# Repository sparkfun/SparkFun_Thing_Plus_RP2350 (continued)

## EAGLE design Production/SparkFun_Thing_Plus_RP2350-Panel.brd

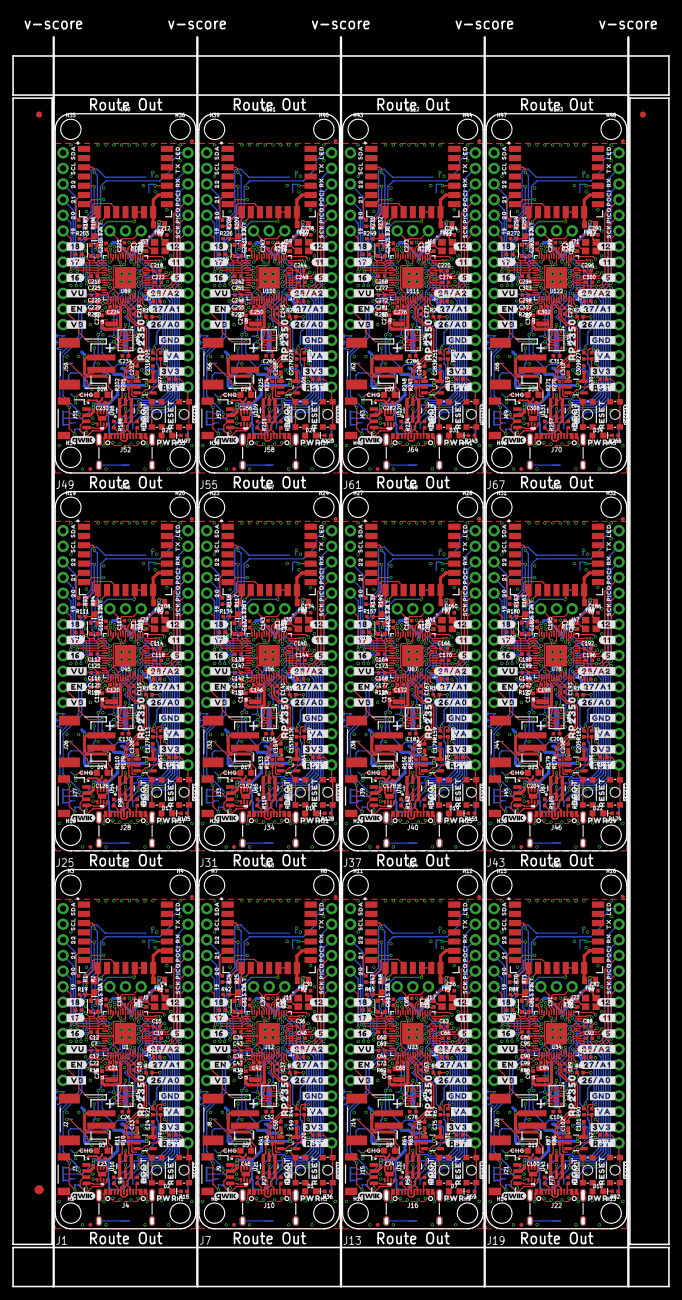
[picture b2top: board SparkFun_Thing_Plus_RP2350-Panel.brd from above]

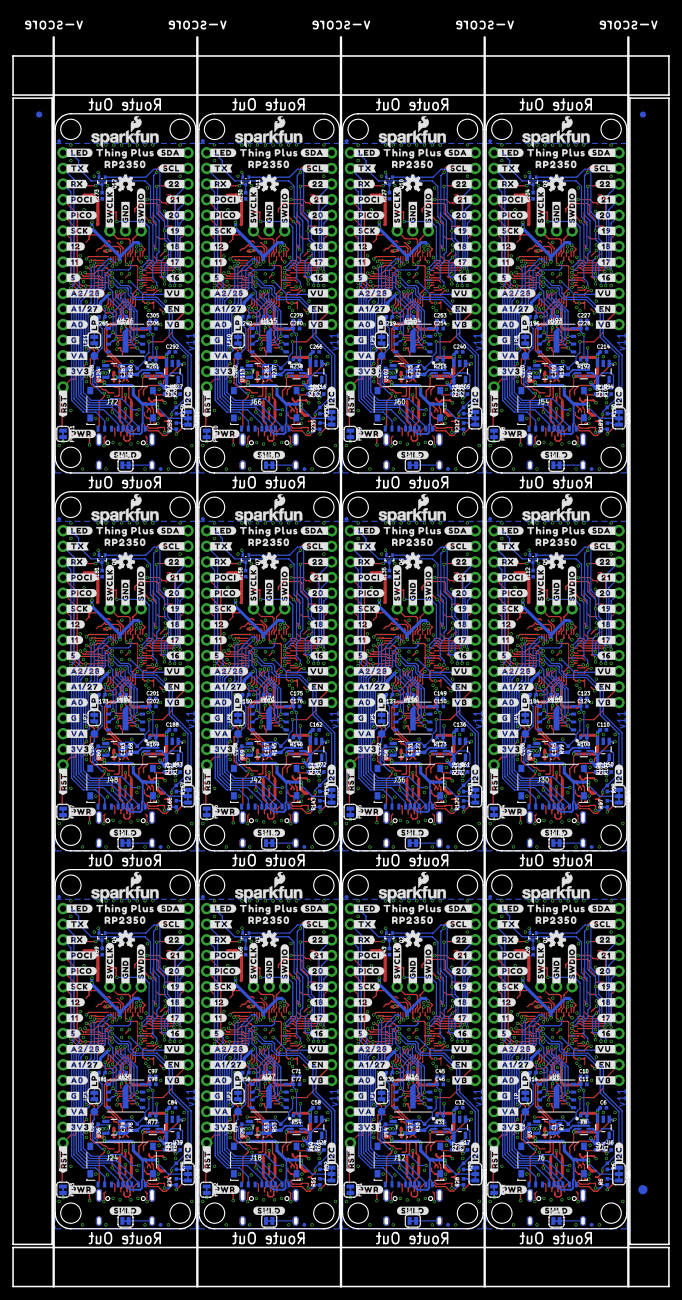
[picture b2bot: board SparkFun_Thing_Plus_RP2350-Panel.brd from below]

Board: 4 copper layers, 106.7 x 203.2 mm, 1950 parts (807 on the bottom side), 912 nets.

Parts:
BOOT, BOOT1, BOOT2, BOOT3, BOOT4, BOOT5, BOOT6, BOOT7, BOOT8, BOOT9, BOOT10, BOOT11: MOMENTARY-SWITCH-SPST-SMD-4.6X2.8MM; TACTILE_SWITCH_SMD_4.6X2.8MM
C1, C2, C5, C6, C10, C13, C22, C27, C28, C31, C32, C45, C47, C50, C53, C54, C57, C58, C71, C73, C76, C79, C80, C83, C84, C97, C99, C102, C105, C106, C109, C110, C123, C125, C128, C131, C132, C135, C136, C149, C151, C154, C157, C158, C161, C162, C175, C177, C180, C183, C184, C187, C188, C201, C203, C206, C209, C210, C213, C214, C227, C229, C232, C235, C236, C239, C240, C253, C255, C258, C261, C262, C265, C266, C279, C281, C284, C287, C288, C291, C292, C305, C307, C310: 2.2uF; 0402-TIGHT
C3, C4, C29, C30, C55, C56, C81, C82, C107, C108, C133, C134, C159, C160, C185, C186, C211, C212, C237, C238, C263, C264, C289, C290: 15pF; 0402-TIGHT
C7, C8, C9, C11, C12, C14, C15, C16, C17, C18, C19, C23, C25, C26, C33, C34, C35, C36, C37, C38, C39, C40, C43, C44, C46, C48, C51, C52, C59, C60, C61, C62, C63, C64, C65, C66, C69, C70, C72, C74, C77, C78, C85, C86, C87, C88, C89, C90, C91, C92, C95, C96, C98, C100, C103, C104, C111, C112, C113, C114, C115, C116, C117, C118, C121, C122, C124, C126, C129, C130, C137, C138, C139, C140, C141, C142, C143, C144, C147, C148, C150, C152, C155, C156, C163, C164, C165, C166, C167, C168, C169, C170, C173, C174, C176, C178, C181, C182, C189, C190, C191, C192, C193, C194, C195, C196, C199, C200, C202, C204, C207, C208, C215, C216, C217, C218, C219, C220, C221, C222, C225, C226, C228, C230, C233, C234, C241, C242, C243, C244, C245, C246, C247, C248, C251, C252, C254, C256, C259, C260, C267, C268, C269, C270, C271, C272, C273, C274, C277, C278, C280, C282, C285, C286, C293, C294, C295, C296, C297, C298, C299, C300, C303, C304, C306, C308, C311, C312: 0.1uF; 0402-TIGHT
C20, C21, C24, C41, C42, C49, C67, C68, C75, C93, C94, C101, C119, C120, C127, C145, C146, C153, C171, C172, C179, C197, C198, C205, C223, C224, C231, C249, C250, C257, C275, C276, C283, C301, C302, C309: 10uF; 0402-TIGHT
D1, D2, D7, D10, D13, D16, D19, D22, D25, D28, D31, D34: Red; LED-0603
D3, D5, D8, D11, D14, D17, D20, D23, D26, D29, D32, D35: Yellow; LED-0603
D4, D6, D9, D12, D15, D18, D21, D24, D27, D30, D33, D36: Blue; LED-0603
E$1, E$2, E$3, E$4: FIDUCIAL-1X2
E$5, E$6: FIDUCIAL-1.5X3
FB1, FB2, FB3, FB4, FB5, FB6, FB7, FB8, FB9, FB10, FB11, FB12: 600Ω; 0805
FD1, FD2, FD3, FD4, FD5, FD6, FD7, FD8, FD9, FD10, FD11, FD12, FD13, FD14, FD15, FD16, FD17, FD18, FD19, FD20, FD21, FD22, FD23, FD24, FD25, FD26, FD27, FD28, FD29, FD30, FD31, FD32, FD33, FD34, FD35, FD36, FD37, FD38, FD39, FD40, FD41, FD42, FD43, FD44, FD45, FD46, FD47, FD48: FIDUCIALUFIDUCIAL; FIDUCIAL-MICRO
H1, H2, H3, H4, H5, H6, H7, H8, H9, H10, H11, H12, H13, H14, H15, H16, H17, H18, H19, H20, H21, H22, H23, H24, H25, H26, H27, H28, H29, H30, H31, H32, H33, H34, H35, H36, H37, H38, H39, H40, H41, H42, H43, H44, H45, H46, H47, H48: STAND-OFF
I2C, I2C1, I2C2, I2C3, I2C4, I2C5, I2C6, I2C7, I2C8, I2C9, I2C10, I2C11: JUMPER-SMT_3_2-NC_TRACE_SILK; SMT-JUMPER_3_2-NC_TRACE_SILK
J1, J7, J13, J19, J25, J31, J37, J43, J49, J55, J61, J67: THING_PLUS_LOGICAL; THING_PLUS
J2, J8, J14, J20, J26, J32, J38, J44, J50, J56, J62, J68: JST-2-SMD
J3, J9, J15, J21, J27, J33, J39, J45, J51, J57, J63, J69: QWIIC_RIGHT_ANGLE; JST04_1MM_RA
J4, J10, J16, J22, J28, J34, J40, J46, J52, J58, J64, J70: USB-C-16P_4LAYER-PADS
J5, J11, J17, J23, J29, J35, J41, J47, J53, J59, J65, J71: 1X03_NO_SILK
J6, J12, J18, J24, J30, J36, J42, J48, J54, J60, J66, J72: MICRO-SD-ATOM; MICROSD_ATOM
L1, L2, L3, L4, L5, L6, L7, L8, L9, L10, L11, L12: 4.7μH; 1008(2520)
LOGO1, LOGO4, LOGO7, LOGO10, LOGO13, LOGO16, LOGO19, LOGO22, LOGO25, LOGO28, LOGO31, LOGO34: SFE_LOGO_NAME_FLAME.1_INCH; SFE_LOGO_NAME_FLAME_.1
LOGO2, LOGO5, LOGO8, LOGO11, LOGO14, LOGO17, LOGO20, LOGO23, LOGO26, LOGO29, LOGO32, LOGO35: OSHW-LOGOS; OSHW-LOGO-S
LOGO3, LOGO6, LOGO9, LOGO12, LOGO15, LOGO18, LOGO21, LOGO24, LOGO27, LOGO30, LOGO33, LOGO36: QWIIC_LOGO_4MM; QWIIC_4MM
LP, LP1, LP2, LP3, LP4, LP5, LP6, LP7, LP8, LP9, LP10, LP11: JUMPER-SMT_2_NC_TRACE_SILK; SMT-JUMPER_2_NC_TRACE_SILK
PWR, PWR1, PWR2, PWR3, PWR4, PWR5, PWR6, PWR7, PWR8, PWR9, PWR10, PWR11: JUMPER-SMT_2_NC_TRACE_SILK; SMT-JUMPER_2_NC_TRACE_SILK
Q1, Q2, Q3, Q4, Q5, Q6, Q7, Q8, Q9, Q10, Q11, Q12: 100mA/20V/3.8Ω; SOT-416FL
R1, R24, R47, R70, R93, R116, R139, R162, R185, R208, R231, R254: 470; 0402-TIGHT
R2, R8, R12, R13, R20, R21, R23, R25, R31, R33, R34, R43, R44, R46, R48, R54, R56, R57, R66, R67, R69, R71, R77, R79, R80, R89, R90, R92, R94, R100, R102, R103, R112, R113, R115, R117, R123, R125, R126, R135, R136, R138, R140, R146, R148, R149, R158, R159, R161, R163, R169, R171, R172, R181, R182, R184, R186, R192, R194, R195, R204, R205, R207, R209, R215, R217, R218, R227, R228, R230, R232, R238, R240, R241, R250, R251, R253, R255, R261, R263, R264, R273, R274, R276: 10k; 0402-TIGHT
R3, R4, R26, R27, R49, R50, R72, R73, R95, R96, R118, R119, R141, R142, R164, R165, R187, R188, R210, R211, R233, R234, R256, R257: 5.1k; 0402-TIGHT
R5, R6, R16, R19, R28, R29, R37, R42, R51, R52, R60, R65, R74, R75, R83, R88, R97, R98, R106, R111, R120, R121, R129, R134, R143, R144, R152, R157, R166, R167, R175, R180, R189, R190, R198, R203, R212, R213, R221, R226, R235, R236, R244, R249, R258, R259, R267, R272: 2.2k; 0402-TIGHT
R7, R22, R30, R45, R53, R68, R76, R91, R99, R114, R122, R137, R145, R160, R168, R183, R191, R206, R214, R229, R237, R252, R260, R275: 1M; 0402-TIGHT
R9, R14, R32, R35, R55, R58, R78, R81, R101, R104, R124, R127, R147, R150, R170, R173, R193, R196, R216, R219, R239, R242, R262, R265: 1k; 0402-TIGHT
R10, R11, R40, R41, R63, R64, R86, R87, R109, R110, R132, R133, R155, R156, R178, R179, R201, R202, R224, R225, R247, R248, R270, R271: 27OHM; 0402-TIGHT
R15, R17, R36, R38, R59, R61, R82, R84, R105, R107, R128, R130, R151, R153, R174, R176, R197, R199, R220, R222, R243, R245, R266, R268: 4.7k; 0402-TIGHT
R18, R39, R62, R85, R108, R131, R154, R177, R200, R223, R246, R269: 10Ω; 0402-TIGHT
RESET, RESET1, RESET2, RESET3, RESET4, RESET5, RESET6, RESET7, RESET8, RESET9, RESET10, RESET11: MOMENTARY-SWITCH-SPST-SMD-4.6X2.8MM; TACTILE_SWITCH_SMD_4.6X2.8MM
SHLD, SHLD1, SHLD2, SHLD3, SHLD4, SHLD5, SHLD6, SHLD7, SHLD8, SHLD9, SHLD10, SHLD11: JUMPER-SMT_2_NC_TRACE_SILK; SMT-JUMPER_2_NC_TRACE_SILK
TP1, TP2, TP3, TP4, TP5, TP6, TP7, TP8, TP9, TP10, TP11, TP12: TEST-POINT3X5; PAD.03X.05
U1, U12, U23, U34, U45, U56, U67, U78, U89, U100, U111, U122: RP2350A
U2, U13, U24, U35, U46, U57, U68, U79, U90, U101, U112, U123: RM2
U3, U9, U14, U20, U25, U31, U36, U42, U47, U53, U58, U64, U69, U75, U80, U86, U91, U97, U102, U108, U113, U119, U124, U130: RT9080-33GJ5; SOT23-5
U4, U15, U26, U37, U48, U59, U70, U81, U92, U103, U114, U125: LM66200; SOT8
U5, U16, U27, U38, U49, U60, U71, U82, U93, U104, U115, U126: W25QXX128MBIT; WSON-8-6X5-SKINNY_CENTERPAD
U6, U17, U28, U39, U50, U61, U72, U83, U94, U105, U116, U127: MCP73831; SOT23-5
U7, U18, U29, U40, U51, U62, U73, U84, U95, U106, U117, U128: WS2812_2020; WS2812-2020
U8, U19, U30, U41, U52, U63, U74, U85, U96, U107, U118, U129: MAX17048; DFN-8
U10, U21, U32, U43, U54, U65, U76, U87, U98, U109, U120, U131: ESD Diode; SOT-23-6
U11, U22, U33, U44, U55, U66, U77, U88, U99, U110, U121, U132: APS6404L-3SQR-ZR
U$1, U$37, U$143, U$214, U$285, U$356, U$427, U$498, U$569, U$640, U$711, U$782: SDA0
U$2, U$71, U$144, U$215, U$286, U$357, U$428, U$499, U$570, U$641, U$712, U$783: SCL0
U$3, U$74, U$145, U$216, U$287, U$358, U$429, U$500, U$571, U$642, U$713, U$784: TX0
U$4, U$75, U$146, U$217, U$288, U$359, U$430, U$501, U$572, U$643, U$714, U$785: RX0
U$5, U$76, U$147, U$218, U$289, U$360, U$431, U$502, U$573, U$644, U$715, U$786: PICO0
U$6, U$77, U$148, U$219, U$290, U$361, U$432, U$503, U$574, U$645, U$716, U$787: POCI0
U$7, U$78, U$149, U$220, U$291, U$362, U$433, U$504, U$575, U$646, U$717, U$788: SCK0
U$8, U$79, U$150, U$221, U$292, U$363, U$434, U$505, U$576, U$647, U$718, U$789: #SDA_#0
U$9, U$80, U$151, U$222, U$293, U$364, U$435, U$506, U$577, U$648, U$719, U$790: #SCL_#0
U$10, U$81, U$152, U$223, U$294, U$365, U$436, U$507, U$578, U$649, U$720, U$791: #_TX#0
U$11, U$82, U$153, U$224, U$295, U$366, U$437, U$508, U$579, U$650, U$721, U$792: #_RX#0
U$12, U$83, U$154, U$225, U$296, U$367, U$438, U$509, U$580, U$651, U$722, U$793: #_POCI#0
U$13, U$84, U$155, U$226, U$297, U$368, U$439, U$510, U$581, U$652, U$723, U$794: #_PICO#0
U$14, U$85, U$156, U$227, U$298, U$369, U$440, U$511, U$582, U$653, U$724, U$795: #_SCK#0
U$15, U$86, U$157, U$228, U$299, U$370, U$441, U$512, U$583, U$654, U$725, U$796: #_GND#0
U$16, U$142, U$213, U$284, U$355, U$426, U$497, U$568, U$639, U$710, U$781, U$852: #_A0#0
U$17, U$87, U$158, U$229, U$300, U$371, U$442, U$513, U$584, U$655, U$726, U$797: #_3V3#0
U$18, U$61, U$125, U$135, U$196, U$206, U$267, U$277, U$338, U$348, U$409, U$419, U$480, U$490, U$551, U$561, U$622, U$632, U$693, U$703, U$764, U$774, U$835, U$845: ##RST#_#0
U$19, U$105, U$176, U$247, U$318, U$389, U$460, U$531, U$602, U$673, U$744, U$815: #I2C#0
U$20, U$88, U$159, U$230, U$301, U$372, U$443, U$514, U$585, U$656, U$727, U$798: #_SWCLK#0
U$21, U$89, U$160, U$231, U$302, U$373, U$444, U$515, U$586, U$657, U$728, U$799: #_SWDIO#0
U$22, U$90, U$161, U$232, U$303, U$374, U$445, U$516, U$587, U$658, U$729, U$800: #_VB#0
U$23, U$91, U$162, U$233, U$304, U$375, U$446, U$517, U$588, U$659, U$730, U$801: #_VU#0
U$24, U$92, U$163, U$234, U$305, U$376, U$447, U$518, U$589, U$660, U$731, U$802: #_EN#0
U$25, U$93, U$164, U$235, U$306, U$377, U$448, U$519, U$590, U$661, U$732, U$803: #3V3_#0
U$26, U$136, U$207, U$278, U$349, U$420, U$491, U$562, U$633, U$704, U$775, U$846: #LP#0
U$27, U$94, U$165, U$236, U$307, U$378, U$449, U$520, U$591, U$662, U$733, U$804: #GND_#0
U$28, U$137, U$208, U$279, U$350, U$421, U$492, U$563, U$634, U$705, U$776, U$847: #11_#0
U$29, U$95, U$166, U$237, U$308, U$379, U$450, U$521, U$592, U$663, U$734, U$805: #26#A0_#0
U$30, U$96, U$167, U$238, U$309, U$380, U$451, U$522, U$593, U$664, U$735, U$806: #27#A1_#0
U$31, U$97, U$168, U$239, U$310, U$381, U$452, U$523, U$594, U$665, U$736, U$807: #28#A2_#0
U$32, U$98, U$169, U$240, U$311, U$382, U$453, U$524, U$595, U$666, U$737, U$808: BOOT0
U$33, U$99, U$170, U$241, U$312, U$383, U$454, U$525, U$596, U$667, U$738, U$809: RESET0
U$34, U$100, U$171, U$242, U$313, U$384, U$455, U$526, U$597, U$668, U$739, U$810: #VU_#0
U$35, U$101, U$172, U$243, U$314, U$385, U$456, U$527, U$598, U$669, U$740, U$811: #VB_#0
U$36, U$102, U$173, U$244, U$315, U$386, U$457, U$528, U$599, U$670, U$741, U$812: #EN_#0
U$38, U$103, U$174, U$245, U$316, U$387, U$458, U$529, U$600, U$671, U$742, U$813: #_A1#27#0
U$39, U$104, U$175, U$246, U$317, U$388, U$459, U$530, U$601, U$672, U$743, U$814: #_A2#28#0
U$40, U$126, U$197, U$268, U$339, U$410, U$481, U$552, U$623, U$694, U$765, U$836: #PWR#0
U$41, U$106, U$177, U$248, U$319, U$390, U$461, U$532, U$603, U$674, U$745, U$816: #SHLD#0
U$42, U$107, U$178, U$249, U$320, U$391, U$462, U$533, U$604, U$675, U$746, U$817: THING_PLUS0
U$43, U$45, U$108, U$109, U$179, U$180, U$250, U$251, U$321, U$322, U$392, U$393, U$463, U$464, U$534, U$535, U$605, U$606, U$676, U$677, U$747, U$748, U$818, U$819: RP23500
U$44, U$141, U$212, U$283, U$354, U$425, U$496, U$567, U$638, U$709, U$780, U$851: #_G#0
U$46, U$110, U$181, U$252, U$323, U$394, U$465, U$536, U$607, U$678, U$749, U$820: #_16#0
U$47, U$111, U$182, U$253, U$324, U$395, U$466, U$537, U$608, U$679, U$750, U$821: #_17#0
U$48, U$112, U$183, U$254, U$325, U$396, U$467, U$538, U$609, U$680, U$751, U$822: #_18#0
U$49, U$124, U$195, U$266, U$337, U$408, U$479, U$550, U$621, U$692, U$763, U$834: CHG0
U$50, U$113, U$184, U$255, U$326, U$397, U$468, U$539, U$610, U$681, U$752, U$823: 200
U$51, U$114, U$185, U$256, U$327, U$398, U$469, U$540, U$611, U$682, U$753, U$824: 210
U$52, U$115, U$186, U$257, U$328, U$399, U$470, U$541, U$612, U$683, U$754, U$825: 220
U$53, U$116, U$187, U$258, U$329, U$400, U$471, U$542, U$613, U$684, U$755, U$826: #22_#0
U$54, U$117, U$188, U$259, U$330, U$401, U$472, U$543, U$614, U$685, U$756, U$827: #21_#0
U$55, U$118, U$189, U$260, U$331, U$402, U$473, U$544, U$615, U$686, U$757, U$828: #20_#0
U$56, U$119, U$190, U$261, U$332, U$403, U$474, U$545, U$616, U$687, U$758, U$829: #19_#0
U$57, U$120, U$191, U$262, U$333, U$404, U$475, U$546, U$617, U$688, U$759, U$830: #18_#0
U$58, U$121, U$192, U$263, U$334, U$405, U$476, U$547, U$618, U$689, U$760, U$831: #17_#0
U$59, U$122, U$193, U$264, U$335, U$406, U$477, U$548, U$619, U$690, U$761, U$832: #16_#0
U$60, U$123, U$194, U$265, U$336, U$407, U$478, U$549, U$620, U$691, U$762, U$833: 190
U$62, U$127, U$198, U$269, U$340, U$411, U$482, U$553, U$624, U$695, U$766, U$837: PWR0
U$63, U$128, U$199, U$270, U$341, U$412, U$483, U$554, U$625, U$696, U$767, U$838: STAT0
U$64, U$129, U$200, U$271, U$342, U$413, U$484, U$555, U$626, U$697, U$768, U$839: #5_#0
U$65, U$138, U$209, U$280, U$351, U$422, U$493, U$564, U$635, U$706, U$777, U$848: #12_#0
U$66, U$139, U$210, U$281, U$352, U$423, U$494, U$565, U$636, U$707, U$778, U$849: #_12#0
U$67, U$130, U$201, U$272, U$343, U$414, U$485, U$556, U$627, U$698, U$769, U$840: LED0
U$68, U$131, U$202, U$273, U$344, U$415, U$486, U$557, U$628, U$699, U$770, U$841: #_LED#0
U$69, U$132, U$203, U$274, U$345, U$416, U$487, U$558, U$629, U$700, U$771, U$842: #_5#0
U$70, U$140, U$211, U$282, U$353, U$424, U$495, U$566, U$637, U$708, U$779, U$850: #_11#0
U$72, U$133, U$204, U$275, U$346, U$417, U$488, U$559, U$630, U$701, U$772, U$843: #VA_#0
U$73, U$134, U$205, U$276, U$347, U$418, U$489, U$560, U$631, U$702, U$773, U$844: #_VA#0
Y1, Y2, Y3, Y4, Y5, Y6, Y7, Y8, Y9, Y10, Y11, Y12: 12MHz; CRYSTAL-SMD-2X2.5MM

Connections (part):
1.1V: C7.1, C18.1, C19.1, C20.1, L1.1, U1.6, U1.23, U1.39, U1.50
1.1V1: C39.1, C40.1, C41.1, C43.1, L2.1, U12.6, U12.23, U12.39, U12.50
1.1V2: C65.1, C66.1, C67.1, C69.1, L3.1, U23.6, U23.23, U23.39, U23.50
1.1V3: C91.1, C92.1, C93.1, C95.1, L4.1, U34.6, U34.23, U34.39, U34.50
1.1V4: C117.1, C118.1, C119.1, C121.1, L5.1, U45.6, U45.23, U45.39, U45.50
1.1V5: C143.1, C144.1, C145.1, C147.1, L6.1, U56.6, U56.23, U56.39, U56.50
1.1V6: C169.1, C170.1, C171.1, C173.1, L7.1, U67.6, U67.23, U67.39, U67.50
1.1V7: C195.1, C196.1, C197.1, C199.1, L8.1, U78.6, U78.23, U78.39, U78.50
1.1V8: C221.1, C222.1, C223.1, C225.1, L9.1, U89.6, U89.23, U89.39, U89.50
1.1V9: C247.1, C248.1, C249.1, C251.1, L10.1, U100.6, U100.23, U100.39, U100.50
1.1V10: C273.1, C274.1, C275.1, C277.1, L11.1, U111.6, U111.23, U111.39, U111.50
1.1V11: C299.1, C300.1, C301.1, C303.1, L12.1, U122.6, U122.23, U122.39, U122.50
3.3V: C2.1, C8.1, C9.1, C10.1, C11.1, C12.1, C14.1, C15.1, C16.1, C17.1, C21.1, C26.1, D2.A, FB1.1, J1.27, LP.2, Q1.2, R8.2, R12.2, R13.2, R18.2, R23.2, U1.1, U1.11, U1.20, U1.30, U1.38, U1.45, U1.49, U1.53, U1.54, U3.5, U5.8, U11.8
3.3V1: C28.1, C33.1, C34.1, C35.1, C36.1, C37.1, C38.1, C42.1, C44.1, C45.1, C46.1, C52.1, D1.A, FB2.1, J7.27, LP1.2, Q2.2, R31.2, R33.2, R34.2, R39.2, R46.2, U12.1, U12.11, U12.20, U12.30, U12.38, U12.45, U12.49, U12.53, U12.54, U14.5, U16.8, U22.8
3.3V2: C54.1, C59.1, C60.1, C61.1, C62.1, C63.1, C64.1, C68.1, C70.1, C71.1, C72.1, C78.1, D7.A, FB3.1, J13.27, LP2.2, Q3.2, R54.2, R56.2, R57.2, R62.2, R69.2, U23.1, U23.11, U23.20, U23.30, U23.38, U23.45, U23.49, U23.53, U23.54, U25.5, U27.8, U33.8
3.3V3: C80.1, C85.1, C86.1, C87.1, C88.1, C89.1, C90.1, C94.1, C96.1, C97.1, C98.1, C104.1, D10.A, FB4.1, J19.27, LP3.2, Q4.2, R77.2, R79.2, R80.2, R85.2, R92.2, U34.1, U34.11, U34.20, U34.30, U34.38, U34.45, U34.49, U34.53, U34.54, U36.5, U38.8, U44.8
3.3V4: C106.1, C111.1, C112.1, C113.1, C114.1, C115.1, C116.1, C120.1, C122.1, C123.1, C124.1, C130.1, D13.A, FB5.1, J25.27, LP4.2, Q5.2, R100.2, R102.2, R103.2, R108.2, R115.2, U45.1, U45.11, U45.20, U45.30, U45.38, U45.45, U45.49, U45.53, U45.54, U47.5, U49.8, U55.8
3.3V5: C132.1, C137.1, C138.1, C139.1, C140.1, C141.1, C142.1, C146.1, C148.1, C149.1, C150.1, C156.1, D16.A, FB6.1, J31.27, LP5.2, Q6.2, R123.2, R125.2, R126.2, R131.2, R138.2, U56.1, U56.11, U56.20, U56.30, U56.38, U56.45, U56.49, U56.53, U56.54, U58.5, U60.8, U66.8
3.3V6: C158.1, C163.1, C164.1, C165.1, C166.1, C167.1, C168.1, C172.1, C174.1, C175.1, C176.1, C182.1, D19.A, FB7.1, J37.27, LP6.2, Q7.2, R146.2, R148.2, R149.2, R154.2, R161.2, U67.1, U67.11, U67.20, U67.30, U67.38, U67.45, U67.49, U67.53, U67.54, U69.5, U71.8, U77.8
3.3V7: C184.1, C189.1, C190.1, C191.1, C192.1, C193.1, C194.1, C198.1, C200.1, C201.1, C202.1, C208.1, D22.A, FB8.1, J43.27, LP7.2, Q8.2, R169.2, R171.2, R172.2, R177.2, R184.2, U78.1, U78.11, U78.20, U78.30, U78.38, U78.45, U78.49, U78.53, U78.54, U80.5, U82.8, U88.8
3.3V8: C210.1, C215.1, C216.1, C217.1, C218.1, C219.1, C220.1, C224.1, C226.1, C227.1, C228.1, C234.1, D25.A, FB9.1, J49.27, LP8.2, Q9.2, R192.2, R194.2, R195.2, R200.2, R207.2, U89.1, U89.11, U89.20, U89.30, U89.38, U89.45, U89.49, U89.53, U89.54, U91.5, U93.8, U99.8
3.3V9: C236.1, C241.1, C242.1, C243.1, C244.1, C245.1, C246.1, C250.1, C252.1, C253.1, C254.1, C260.1, D28.A, FB10.1, J55.27, LP9.2, Q10.2, R215.2, R217.2, R218.2, R223.2, R230.2, U100.1, U100.11, U100.20, U100.30, U100.38, U100.45, U100.49, U100.53, U100.54, U102.5, U104.8, U110.8
3.3V10: C262.1, C267.1, C268.1, C269.1, C270.1, C271.1, C272.1, C276.1, C278.1, C279.1, C280.1, C286.1, D31.A, FB11.1, J61.27, LP10.2, Q11.2, R238.2, R240.2, R241.2, R246.2, R253.2, U111.1, U111.11, U111.20, U111.30, U111.38, U111.45, U111.49, U111.53, U111.54, U113.5, U115.8, U121.8
3.3V11: C288.1, C293.1, C294.1, C295.1, C296.1, C297.1, C298.1, C302.1, C304.1, C305.1, C306.1, C312.1, D34.A, FB12.1, J67.27, LP11.2, Q12.2, R261.2, R263.2, R264.2, R269.2, R276.2, U122.1, U122.11, U122.20, U122.30, U122.38, U122.45, U122.49, U122.53, U122.54, U124.5, U126.8, U132.8
3.3V_SW: C24.1, C25.1, I2C.2, J3.2, J6.4, U7.VCC, U9.5
3.3V_SW1: C49.1, C51.1, I2C1.2, J9.2, J12.4, U18.VCC, U20.5
3.3V_SW2: C75.1, C77.1, I2C2.2, J15.2, J18.4, U29.VCC, U31.5
3.3V_SW3: C101.1, C103.1, I2C3.2, J21.2, J24.4, U40.VCC, U42.5
3.3V_SW4: C127.1, C129.1, I2C4.2, J27.2, J30.4, U51.VCC, U53.5
3.3V_SW5: C153.1, C155.1, I2C5.2, J33.2, J36.4, U62.VCC, U64.5
3.3V_SW6: C179.1, C181.1, I2C6.2, J39.2, J42.4, U73.VCC, U75.5
3.3V_SW7: C205.1, C207.1, I2C7.2, J45.2, J48.4, U84.VCC, U86.5
3.3V_SW8: C231.1, C233.1, I2C8.2, J51.2, J54.4, U95.VCC, U97.5
3.3V_SW9: C257.1, C259.1, I2C9.2, J57.2, J60.4, U106.VCC, U108.5
3.3V_SW10: C283.1, C285.1, I2C10.2, J63.2, J66.4, U117.VCC, U119.5
3.3V_SW11: C309.1, C311.1, I2C11.2, J69.2, J72.4, U128.VCC, U130.5
!BATT_ALERT!: U1.19, U8.5
!BATT_ALERT!1: U12.19, U19.5
!BATT_ALERT!2: U23.19, U30.5
!BATT_ALERT!3: U34.19, U41.5
!BATT_ALERT!4: U45.19, U52.5
!BATT_ALERT!5: U56.19, U63.5
!BATT_ALERT!6: U67.19, U74.5
!BATT_ALERT!7: U78.19, U85.5
!BATT_ALERT!8: U89.19, U96.5
!BATT_ALERT!9: U100.19, U107.5
!BATT_ALERT!10: U111.19, U118.5
!BATT_ALERT!11: U122.19, U129.5
!BOOT!: BOOT.3, BOOT.4, R14.2, TP1.1
!BOOT!1: BOOT1.3, BOOT1.4, R35.2, TP2.1
!BOOT!2: BOOT2.3, BOOT2.4, R58.2, TP3.1
!BOOT!3: BOOT3.3, BOOT3.4, R81.2, TP4.1
!BOOT!4: BOOT4.3, BOOT4.4, R104.2, TP5.1
!BOOT!5: BOOT5.3, BOOT5.4, R127.2, TP6.1
!BOOT!6: BOOT6.3, BOOT6.4, R150.2, TP7.1
!BOOT!7: BOOT7.3, BOOT7.4, R173.2, TP8.1
!BOOT!8: BOOT8.3, BOOT8.4, R196.2, TP9.1
!BOOT!9: BOOT9.3, BOOT9.4, R219.2, TP10.1
!BOOT!10: BOOT10.3, BOOT10.4, R242.2, TP11.1
!BOOT!11: BOOT11.3, BOOT11.4, R265.2, TP12.1
!RESET!: J1.28, R12.1, RESET.3, RESET.4, U1.26
!RESET!1: J7.28, R33.1, RESET1.3, RESET1.4, U12.26
!RESET!2: J13.28, R56.1, RESET2.3, RESET2.4, U23.26
!RESET!3: J19.28, R79.1, RESET3.3, RESET3.4, U34.26
!RESET!4: J25.28, R102.1, RESET4.3, RESET4.4, U45.26
!RESET!5: J31.28, R125.1, RESET5.3, RESET5.4, U56.26
!RESET!6: J37.28, R148.1, RESET6.3, RESET6.4, U67.26
!RESET!7: J43.28, R171.1, RESET7.3, RESET7.4, U78.26
!RESET!8: J49.28, R194.1, RESET8.3, RESET8.4, U89.26
!RESET!9: J55.28, R217.1, RESET9.3, RESET9.4, U100.26
!RESET!10: J61.28, R240.1, RESET10.3, RESET10.4, U111.26
!RESET!11: J67.28, R263.1, RESET11.3, RESET11.4, U122.26
BAT_SW: Q1.1, R8.1, U4.8
BAT_SW1: Q2.1, R31.1, U15.8
BAT_SW2: Q3.1, R54.1, U26.8
BAT_SW3: Q4.1, R77.1, U37.8
BAT_SW4: Q5.1, R100.1, U48.8
BAT_SW5: Q6.1, R123.1, U59.8
BAT_SW6: Q7.1, R146.1, U70.8
BAT_SW7: Q8.1, R169.1, U81.8
BAT_SW8: Q9.1, R192.1, U92.8
BAT_SW9: Q10.1, R215.1, U103.8
BAT_SW10: Q11.1, R238.1, U114.8
BAT_SW11: Q12.1, R261.1, U125.8
EN: J1.11, R7.2, U3.3
EN1: J7.11, R30.2, U14.3
EN2: J13.11, R53.2, U25.3
EN3: J19.11, R76.2, U36.3
EN4: J25.11, R99.2, U47.3
EN5: J31.11, R122.2, U58.3
EN6: J37.11, R145.2, U69.3
EN7: J43.11, R168.2, U80.3
EN8: J49.11, R191.2, U91.3
EN9: J55.11, R214.2, U102.3
EN10: J61.11, R237.2, U113.3
EN11: J67.11, R260.2, U124.3
GND: BOOT.1, BOOT.2, C1.2, C2.2, C3.1, C4.2, C5.2, C6.2, C7.2, C8.2, C9.2, C10.2, C11.2, C12.2, C13.2, C14.2, C15.2, C16.2, C17.2, C18.2, C19.2, C20.2, C21.2, C22.2, C23.2, C24.2, C25.2, C26.2, J1.25, J2.1, J3.1, J4.GND, J4.GND2, J5.2, J6.6, J6.SHIELD1, J6.SHIELD2, J6.SHIELD3, J6.SHIELD4, PWR.1, R3.1, R4.1, R16.1, R19.1, R20.1, R22.1, RESET.1, RESET.2, SHLD.1, U1.47, U1.EPAD, U2.A1, U2.A4, U2.A7, U2.B4, U2.C1, U2.C7, U3.2, U4.1, U4.4, U4.5, U5.4, U6.2, U7.GND, U8.1, U8.4, U8.6, U8.9, U9.2, U10.2, U11.4, U11.9
GND1: BOOT1.1, BOOT1.2, C27.2, C28.2, C29.1, C30.2, C31.2, C32.2, C33.2, C34.2, C35.2, C36.2, C37.2, C38.2, C39.2, C40.2, C41.2, C42.2, C43.2, C44.2, C45.2, C46.2, C47.2, C48.2, C49.2, C50.2, C51.2, C52.2, J7.25, J8.1, J9.1, J10.GND, J10.GND2, J11.2, J12.6, J12.SHIELD1, J12.SHIELD2, J12.SHIELD3, J12.SHIELD4, PWR1.1, R26.1, R27.1, R37.1, R42.1, R43.1, R45.1, RESET1.1, RESET1.2, SHLD1.1, U12.47, U12.EPAD, U13.A1, U13.A4, U13.A7, U13.B4, U13.C1, U13.C7, U14.2, U15.1, U15.4, U15.5, U16.4, U17.2, U18.GND, U19.1, U19.4, U19.6, U19.9, U20.2, U21.2, U22.4, U22.9
GND2: BOOT2.1, BOOT2.2, C53.2, C54.2, C55.1, C56.2, C57.2, C58.2, C59.2, C60.2, C61.2, C62.2, C63.2, C64.2, C65.2, C66.2, C67.2, C68.2, C69.2, C70.2, C71.2, C72.2, C73.2, C74.2, C75.2, C76.2, C77.2, C78.2, J13.25, J14.1, J15.1, J16.GND, J16.GND2, J17.2, J18.6, J18.SHIELD1, J18.SHIELD2, J18.SHIELD3, J18.SHIELD4, PWR2.1, R49.1, R50.1, R60.1, R65.1, R66.1, R68.1, RESET2.1, RESET2.2, SHLD2.1, U23.47, U23.EPAD, U24.A1, U24.A4, U24.A7, U24.B4, U24.C1, U24.C7, U25.2, U26.1, U26.4, U26.5, U27.4, U28.2, U29.GND, U30.1, U30.4, U30.6, U30.9, U31.2, U32.2, U33.4, U33.9
GND3: BOOT3.1, BOOT3.2, C79.2, C80.2, C81.1, C82.2, C83.2, C84.2, C85.2, C86.2, C87.2, C88.2, C89.2, C90.2, C91.2, C92.2, C93.2, C94.2, C95.2, C96.2, C97.2, C98.2, C99.2, C100.2, C101.2, C102.2, C103.2, C104.2, J19.25, J20.1, J21.1, J22.GND, J22.GND2, J23.2, J24.6, J24.SHIELD1, J24.SHIELD2, J24.SHIELD3, J24.SHIELD4, PWR3.1, R72.1, R73.1, R83.1, R88.1, R89.1, R91.1, RESET3.1, RESET3.2, SHLD3.1, U34.47, U34.EPAD, U35.A1, U35.A4, U35.A7, U35.B4, U35.C1, U35.C7, U36.2, U37.1, U37.4, U37.5, U38.4, U39.2, U40.GND, U41.1, U41.4, U41.6, U41.9, U42.2, U43.2, U44.4, U44.9
GND4: BOOT4.1, BOOT4.2, C105.2, C106.2, C107.1, C108.2, C109.2, C110.2, C111.2, C112.2, C113.2, C114.2, C115.2, C116.2, C117.2, C118.2, C119.2, C120.2, C121.2, C122.2, C123.2, C124.2, C125.2, C126.2, C127.2, C128.2, C129.2, C130.2, J25.25, J26.1, J27.1, J28.GND, J28.GND2, J29.2, J30.6, J30.SHIELD1, J30.SHIELD2, J30.SHIELD3, J30.SHIELD4, PWR4.1, R95.1, R96.1, R106.1, R111.1, R112.1, R114.1, RESET4.1, RESET4.2, SHLD4.1, U45.47, U45.EPAD, U46.A1, U46.A4, U46.A7, U46.B4, U46.C1, U46.C7, U47.2, U48.1, U48.4, U48.5, U49.4, U50.2, U51.GND, U52.1, U52.4, U52.6, U52.9, U53.2, U54.2, U55.4, U55.9
GND5: BOOT5.1, BOOT5.2, C131.2, C132.2, C133.1, C134.2, C135.2, C136.2, C137.2, C138.2, C139.2, C140.2, C141.2, C142.2, C143.2, C144.2, C145.2, C146.2, C147.2, C148.2, C149.2, C150.2, C151.2, C152.2, C153.2, C154.2, C155.2, C156.2, J31.25, J32.1, J33.1, J34.GND, J34.GND2, J35.2, J36.6, J36.SHIELD1, J36.SHIELD2, J36.SHIELD3, J36.SHIELD4, PWR5.1, R118.1, R119.1, R129.1, R134.1, R135.1, R137.1, RESET5.1, RESET5.2, SHLD5.1, U56.47, U56.EPAD, U57.A1, U57.A4, U57.A7, U57.B4, U57.C1, U57.C7, U58.2, U59.1, U59.4, U59.5, U60.4, U61.2, U62.GND, U63.1, U63.4, U63.6, U63.9, U64.2, U65.2, U66.4, U66.9
GND6: BOOT6.1, BOOT6.2, C157.2, C158.2, C159.1, C160.2, C161.2, C162.2, C163.2, C164.2, C165.2, C166.2, C167.2, C168.2, C169.2, C170.2, C171.2, C172.2, C173.2, C174.2, C175.2, C176.2, C177.2, C178.2, C179.2, C180.2, C181.2, C182.2, J37.25, J38.1, J39.1, J40.GND, J40.GND2, J41.2, J42.6, J42.SHIELD1, J42.SHIELD2, J42.SHIELD3, J42.SHIELD4, PWR6.1, R141.1, R142.1, R152.1, R157.1, R158.1, R160.1, RESET6.1, RESET6.2, SHLD6.1, U67.47, U67.EPAD, U68.A1, U68.A4, U68.A7, U68.B4, U68.C1, U68.C7, U69.2, U70.1, U70.4, U70.5, U71.4, U72.2, U73.GND, U74.1, U74.4, U74.6, U74.9, U75.2, U76.2, U77.4, U77.9
GND7: BOOT7.1, BOOT7.2, C183.2, C184.2, C185.1, C186.2, C187.2, C188.2, C189.2, C190.2, C191.2, C192.2, C193.2, C194.2, C195.2, C196.2, C197.2, C198.2, C199.2, C200.2, C201.2, C202.2, C203.2, C204.2, C205.2, C206.2, C207.2, C208.2, J43.25, J44.1, J45.1, J46.GND, J46.GND2, J47.2, J48.6, J48.SHIELD1, J48.SHIELD2, J48.SHIELD3, J48.SHIELD4, PWR7.1, R164.1, R165.1, R175.1, R180.1, R181.1, R183.1, RESET7.1, RESET7.2, SHLD7.1, U78.47, U78.EPAD, U79.A1, U79.A4, U79.A7, U79.B4, U79.C1, U79.C7, U80.2, U81.1, U81.4, U81.5, U82.4, U83.2, U84.GND, U85.1, U85.4, U85.6, U85.9, U86.2, U87.2, U88.4, U88.9
GND8: BOOT8.1, BOOT8.2, C209.2, C210.2, C211.1, C212.2, C213.2, C214.2, C215.2, C216.2, C217.2, C218.2, C219.2, C220.2, C221.2, C222.2, C223.2, C224.2, C225.2, C226.2, C227.2, C228.2, C229.2, C230.2, C231.2, C232.2, C233.2, C234.2, J49.25, J50.1, J51.1, J52.GND, J52.GND2, J53.2, J54.6, J54.SHIELD1, J54.SHIELD2, J54.SHIELD3, J54.SHIELD4, PWR8.1, R187.1, R188.1, R198.1, R203.1, R204.1, R206.1, RESET8.1, RESET8.2, SHLD8.1, U89.47, U89.EPAD, U90.A1, U90.A4, U90.A7, U90.B4, U90.C1, U90.C7, U91.2, U92.1, U92.4, U92.5, U93.4, U94.2, U95.GND, U96.1, U96.4, U96.6, U96.9, U97.2, U98.2, U99.4, U99.9
GND9: BOOT9.1, BOOT9.2, C235.2, C236.2, C237.1, C238.2, C239.2, C240.2, C241.2, C242.2, C243.2, C244.2, C245.2, C246.2, C247.2, C248.2, C249.2, C250.2, C251.2, C252.2, C253.2, C254.2, C255.2, C256.2, C257.2, C258.2, C259.2, C260.2, J55.25, J56.1, J57.1, J58.GND, J58.GND2, J59.2, J60.6, J60.SHIELD1, J60.SHIELD2, J60.SHIELD3, J60.SHIELD4, PWR9.1, R210.1, R211.1, R221.1, R226.1, R227.1, R229.1, RESET9.1, RESET9.2, SHLD9.1, U100.47, U100.EPAD, U101.A1, U101.A4, U101.A7, U101.B4, U101.C1, U101.C7, U102.2, U103.1, U103.4, U103.5, U104.4, U105.2, U106.GND, U107.1, U107.4, U107.6, U107.9, U108.2, U109.2, U110.4, U110.9
GND10: BOOT10.1, BOOT10.2, C261.2, C262.2, C263.1, C264.2, C265.2, C266.2, C267.2, C268.2, C269.2, C270.2, C271.2, C272.2, C273.2, C274.2, C275.2, C276.2, C277.2, C278.2, C279.2, C280.2, C281.2, C282.2, C283.2, C284.2, C285.2, C286.2, J61.25, J62.1, J63.1, J64.GND, J64.GND2, J65.2, J66.6, J66.SHIELD1, J66.SHIELD2, J66.SHIELD3, J66.SHIELD4, PWR10.1, R233.1, R234.1, R244.1, R249.1, R250.1, R252.1, RESET10.1, RESET10.2, SHLD10.1, U111.47, U111.EPAD, U112.A1, U112.A4, U112.A7, U112.B4, U112.C1, U112.C7, U113.2, U114.1, U114.4, U114.5, U115.4, U116.2, U117.GND, U118.1, U118.4, U118.6, U118.9, U119.2, U120.2, U121.4, U121.9
GND11: BOOT11.1, BOOT11.2, C287.2, C288.2, C289.1, C290.2, C291.2, C292.2, C293.2, C294.2, C295.2, C296.2, C297.2, C298.2, C299.2, C300.2, C301.2, C302.2, C303.2, C304.2, C305.2, C306.2, C307.2, C308.2, C309.2, C310.2, C311.2, C312.2, J67.25, J68.1, J69.1, J70.GND, J70.GND2, J71.2, J72.6, J72.SHIELD1, J72.SHIELD2, J72.SHIELD3, J72.SHIELD4, PWR11.1, R256.1, R257.1, R267.1, R272.1, R273.1, R275.1, RESET11.1, RESET11.2, SHLD11.1, U122.47, U122.EPAD, U123.A1, U123.A4, U123.A7, U123.B4, U123.C1, U123.C7, U124.2, U125.1, U125.4, U125.5, U126.4, U127.2, U128.GND, U129.1, U129.4, U129.6, U129.9, U130.2, U131.2, U132.4, U132.9
GPIO1: J7.3, U12.34
GPIO2: J7.4, U12.33
GPIO3: J7.5, U12.32
GPIO4: J7.6, U12.31
GPIO5: J1.21, U1.8
GPIO6: J7.7, U12.29
GPIO7: J7.8, U12.28
GPIO8: J7.9, U12.27
GPIO9: J7.21, U12.8
GPIO10: J7.20, U12.15
GPIO11: J1.20, U1.15
GPIO12: J1.19, U1.16
GPIO13: J7.19, U12.16
GPIO14: J13.3, U23.34
GPIO15: J13.4, U23.33
GPIO16: J1.9, U1.27
GPIO17: J1.8, U1.28
GPIO18: J1.7, U1.29
GPIO19: J1.6, U1.31
GPIO20: J1.5, U1.32
GPIO21: J1.4, U1.33
GPIO22: J1.3, U1.34
GPIO23: J13.5, U23.32
GPIO24: J13.6, U23.31
GPIO25: J13.7, U23.29
GPIO26: J13.8, U23.28
GPIO26/A0: J1.24, U1.40
GPIO26/A1: J7.24, U12.40
GPIO26/A2: J13.24, U23.40
GPIO26/A3: J19.24, U34.40
GPIO26/A4: J25.24, U45.40
GPIO26/A5: J31.24, U56.40
GPIO26/A6: J37.24, U67.40
GPIO26/A7: J43.24, U78.40
GPIO26/A8: J49.24, U89.40
GPIO26/A9: J55.24, U100.40
GPIO26/A10: J61.24, U111.40
GPIO26/A11: J67.24, U122.40
GPIO27: J13.9, U23.27
GPIO27/A1: J1.23, U1.41
GPIO27/A2: J7.23, U12.41
GPIO27/A3: J13.23, U23.41
GPIO27/A4: J19.23, U34.41
GPIO27/A5: J25.23, U45.41
GPIO27/A6: J31.23, U56.41
GPIO27/A7: J37.23, U67.41
GPIO27/A8: J43.23, U78.41
GPIO27/A9: J49.23, U89.41
GPIO27/A10: J55.23, U100.41
GPIO27/A11: J61.23, U111.41
GPIO27/A12: J67.23, U122.41
GPIO28: J13.21, U23.8
GPIO28/A1: J7.22, U12.42
GPIO28/A2: J1.22, U1.42
GPIO28/A3: J13.22, U23.42
GPIO28/A4: J19.22, U34.42
GPIO28/A5: J25.22, U45.42
GPIO28/A6: J31.22, U56.42
GPIO28/A7: J37.22, U67.42
GPIO28/A8: J43.22, U78.42
GPIO28/A9: J49.22, U89.42
GPIO28/A10: J55.22, U100.42
GPIO28/A11: J61.22, U111.42
GPIO28/A12: J67.22, U122.42
GPIO29: J13.20, U23.15
GPIO30: J13.19, U23.16
GPIO31: J19.3, U34.34
GPIO32: J19.4, U34.33
GPIO33: J19.5, U34.32
GPIO34: J19.6, U34.31
GPIO35: J19.7, U34.29
GPIO36: J19.8, U34.28
GPIO37: J19.9, U34.27
GPIO38: J19.21, U34.8
GPIO39: J19.20, U34.15
GPIO40: J19.19, U34.16
GPIO41: J25.3, U45.34
GPIO42: J25.4, U45.33
GPIO43: J25.5, U45.32
GPIO44: J25.6, U45.31
GPIO45: J25.7, U45.29
GPIO46: J25.8, U45.28
GPIO47: J25.9, U45.27
GPIO48: J25.21, U45.8
GPIO49: J25.20, U45.15
GPIO50: J25.19, U45.16
GPIO51: J31.3, U56.34
GPIO52: J31.4, U56.33
GPIO53: J31.5, U56.32
GPIO54: J31.6, U56.31
GPIO55: J31.7, U56.29
GPIO56: J31.8, U56.28
GPIO57: J31.9, U56.27
GPIO58: J31.21, U56.8
GPIO59: J31.20, U56.15
GPIO60: J31.19, U56.16
GPIO61: J37.3, U67.34
GPIO62: J37.4, U67.33
GPIO63: J37.5, U67.32
GPIO64: J37.6, U67.31
GPIO65: J37.7, U67.29
GPIO66: J37.8, U67.28
GPIO67: J37.9, U67.27
GPIO68: J37.21, U67.8
GPIO69: J37.20, U67.15
GPIO70: J37.19, U67.16
GPIO71: J43.3, U78.34
GPIO72: J43.4, U78.33
GPIO73: J43.5, U78.32
GPIO74: J43.6, U78.31
GPIO75: J43.7, U78.29
GPIO76: J43.8, U78.28
GPIO77: J43.9, U78.27
GPIO78: J43.21, U78.8
GPIO79: J43.20, U78.15
GPIO80: J43.19, U78.16
GPIO81: J49.3, U89.34
GPIO82: J49.4, U89.33
GPIO83: J49.5, U89.32
GPIO84: J49.6, U89.31
GPIO85: J49.7, U89.29
GPIO86: J49.8, U89.28
GPIO87: J49.9, U89.27
GPIO88: J49.21, U89.8
GPIO89: J49.20, U89.15
GPIO90: J49.19, U89.16
GPIO91: J55.3, U100.34
GPIO92: J55.4, U100.33
GPIO93: J55.5, U100.32
GPIO94: J55.6, U100.31
GPIO95: J55.7, U100.29
GPIO96: J55.8, U100.28
GPIO97: J55.9, U100.27
GPIO98: J55.21, U100.8
GPIO99: J55.20, U100.15
GPIO100: J55.19, U100.16
GPIO101: J61.3, U111.34
GPIO102: J61.4, U111.33
GPIO103: J61.5, U111.32
GPIO104: J61.6, U111.31
GPIO105: J61.7, U111.29
GPIO106: J61.8, U111.28
GPIO107: J61.9, U111.27
GPIO108: J61.21, U111.8
GPIO109: J61.20, U111.15
GPIO110: J61.19, U111.16
GPIO111: J67.3, U122.34
GPIO112: J67.4, U122.33
GPIO113: J67.5, U122.32
GPIO114: J67.6, U122.31
GPIO115: J67.7, U122.29
GPIO116: J67.8, U122.28
GPIO117: J67.9, U122.27
GPIO118: J67.21, U122.8
GPIO119: J67.20, U122.15
GPIO120: J67.19, U122.16
LED_IN: U1.18, U7.DI
LED_IN1: U12.18, U18.DI
LED_IN2: U23.18, U29.DI
LED_IN3: U34.18, U40.DI
LED_IN4: U45.18, U51.DI
LED_IN5: U56.18, U62.DI
LED_IN6: U67.18, U73.DI
LED_IN7: U78.18, U84.DI
LED_IN8: U89.18, U95.DI
LED_IN9: U100.18, U106.DI
LED_IN10: U111.18, U117.DI
LED_IN11: U122.18, U128.DI
LED_OUT: J1.13, U7.DO
LED_OUT1: J7.13, U18.DO
LED_OUT2: J13.13, U29.DO
LED_OUT3: J19.13, U40.DO
LED_OUT4: J25.13, U51.DO
LED_OUT5: J31.13, U62.DO
LED_OUT6: J37.13, U73.DO
LED_OUT7: J43.13, U84.DO
LED_OUT8: J49.13, U95.DO
LED_OUT9: J55.13, U106.DO
LED_OUT10: J61.13, U117.DO
LED_OUT11: J67.13, U128.DO
unnamed: FB1.2, U2.B7, U2.C2
unnamed: R1.1, U2.A6
unnamed: R2.1, U2.B3
unnamed: D4.C, R19.2
unnamed: J4.B5, R3.2
unnamed: J4.A5, R4.2
unnamed: J4.A7, J4.B7, R11.1, U10.1, U10.6
unnamed: J4.A6, J4.B6, R10.1, U10.3, U10.4
unnamed: I2C.3, R5.2
unnamed: I2C.1, R6.2
unnamed: LP.1, R21.2
unnamed: FB2.2, U13.B7, U13.C2
unnamed: C3.2, U1.21, Y1.P3
unnamed: C4.1, R9.1, Y1.P1
unnamed: R9.2, U1.22
unnamed: R24.1, U13.A6
unnamed: R25.1, U13.B3
unnamed: D2.C, R15.2
unnamed: PWR.2, R15.1
unnamed: R16.2, U6.5
unnamed: D3.A, R17.1
unnamed: D3.C, U6.1
unnamed: L1.2, U1.48
unnamed: J10.B5, R26.2
unnamed: J10.A5, R27.2
unnamed: J10.A7, J10.B7, R41.1, U21.1, U21.6
unnamed: J10.A6, J10.B6, R40.1, U21.3, U21.4
unnamed: I2C1.3, R28.2
unnamed: I2C1.1, R29.2
unnamed: C29.2, U12.21, Y2.P3
unnamed: C30.1, R32.1, Y2.P1
unnamed: R32.2, U12.22
unnamed: D1.C, R36.2
unnamed: PWR1.2, R36.1
unnamed: R37.2, U17.5
unnamed: D5.A, R38.1
unnamed: D5.C, U17.1
unnamed: L2.2, U12.48
unnamed: D6.C, R42.2
unnamed: LP1.1, R44.2
unnamed: FB3.2, U24.B7, U24.C2
unnamed: R47.1, U24.A6
unnamed: R48.1, U24.B3
unnamed: J16.B5, R49.2
unnamed: J16.A5, R50.2
unnamed: J16.A7, J16.B7, R64.1, U32.1, U32.6
unnamed: J16.A6, J16.B6, R63.1, U32.3, U32.4
unnamed: I2C2.3, R51.2
unnamed: I2C2.1, R52.2
unnamed: C55.2, U23.21, Y3.P3
unnamed: C56.1, R55.1, Y3.P1
unnamed: R55.2, U23.22
unnamed: D7.C, R59.2
unnamed: PWR2.2, R59.1
unnamed: R60.2, U28.5
unnamed: D8.A, R61.1
unnamed: D8.C, U28.1
unnamed: L3.2, U23.48
unnamed: D9.C, R65.2
unnamed: LP2.1, R67.2
unnamed: FB4.2, U35.B7, U35.C2
unnamed: R70.1, U35.A6
unnamed: R71.1, U35.B3
unnamed: J22.B5, R72.2
unnamed: J22.A5, R73.2
unnamed: J22.A7, J22.B7, R87.1, U43.1, U43.6
unnamed: J22.A6, J22.B6, R86.1, U43.3, U43.4
unnamed: I2C3.3, R74.2
unnamed: I2C3.1, R75.2
unnamed: C81.2, U34.21, Y4.P3
unnamed: C82.1, R78.1, Y4.P1
unnamed: R78.2, U34.22
unnamed: D10.C, R82.2
unnamed: PWR3.2, R82.1
unnamed: R83.2, U39.5
unnamed: D11.A, R84.1
unnamed: D11.C, U39.1
unnamed: L4.2, U34.48
unnamed: D12.C, R88.2
unnamed: LP3.1, R90.2
unnamed: FB5.2, U46.B7, U46.C2
unnamed: R93.1, U46.A6
unnamed: R94.1, U46.B3
unnamed: J28.B5, R95.2
unnamed: J28.A5, R96.2
unnamed: J28.A7, J28.B7, R110.1, U54.1, U54.6
unnamed: J28.A6, J28.B6, R109.1, U54.3, U54.4
unnamed: I2C4.3, R97.2
unnamed: I2C4.1, R98.2
unnamed: C107.2, U45.21, Y5.P3
unnamed: C108.1, R101.1, Y5.P1
unnamed: R101.2, U45.22
unnamed: D13.C, R105.2
unnamed: PWR4.2, R105.1
unnamed: R106.2, U50.5
unnamed: D14.A, R107.1
unnamed: D14.C, U50.1
unnamed: L5.2, U45.48
unnamed: D15.C, R111.2
unnamed: LP4.1, R113.2
unnamed: FB6.2, U57.B7, U57.C2
unnamed: R116.1, U57.A6
unnamed: R117.1, U57.B3
unnamed: J34.B5, R118.2
unnamed: J34.A5, R119.2
unnamed: J34.A7, J34.B7, R133.1, U65.1, U65.6
unnamed: J34.A6, J34.B6, R132.1, U65.3, U65.4
unnamed: I2C5.3, R120.2
unnamed: I2C5.1, R121.2
unnamed: C133.2, U56.21, Y6.P3
unnamed: C134.1, R124.1, Y6.P1
unnamed: R124.2, U56.22
unnamed: D16.C, R128.2
unnamed: PWR5.2, R128.1
unnamed: R129.2, U61.5
unnamed: D17.A, R130.1
unnamed: D17.C, U61.1
unnamed: L6.2, U56.48
unnamed: D18.C, R134.2
unnamed: LP5.1, R136.2
unnamed: FB7.2, U68.B7, U68.C2
unnamed: R139.1, U68.A6
unnamed: R140.1, U68.B3
unnamed: J40.B5, R141.2
unnamed: J40.A5, R142.2
unnamed: J40.A7, J40.B7, R156.1, U76.1, U76.6
unnamed: J40.A6, J40.B6, R155.1, U76.3, U76.4
unnamed: I2C6.3, R143.2
unnamed: I2C6.1, R144.2
unnamed: C159.2, U67.21, Y7.P3
unnamed: C160.1, R147.1, Y7.P1
unnamed: R147.2, U67.22
unnamed: D19.C, R151.2
unnamed: PWR6.2, R151.1
unnamed: R152.2, U72.5
unnamed: D20.A, R153.1
unnamed: D20.C, U72.1
unnamed: L7.2, U67.48
unnamed: D21.C, R157.2
unnamed: LP6.1, R159.2
unnamed: FB8.2, U79.B7, U79.C2
unnamed: R162.1, U79.A6
unnamed: R163.1, U79.B3
unnamed: J46.B5, R164.2
unnamed: J46.A5, R165.2
unnamed: J46.A7, J46.B7, R179.1, U87.1, U87.6
unnamed: J46.A6, J46.B6, R178.1, U87.3, U87.4
unnamed: I2C7.3, R166.2
unnamed: I2C7.1, R167.2
unnamed: C185.2, U78.21, Y8.P3
unnamed: C186.1, R170.1, Y8.P1
unnamed: R170.2, U78.22
unnamed: D22.C, R174.2
unnamed: PWR7.2, R174.1
unnamed: R175.2, U83.5
unnamed: D23.A, R176.1
unnamed: D23.C, U83.1
unnamed: L8.2, U78.48
unnamed: D24.C, R180.2
unnamed: LP7.1, R182.2
unnamed: FB9.2, U90.B7, U90.C2
unnamed: R185.1, U90.A6
unnamed: R186.1, U90.B3
unnamed: J52.B5, R187.2
unnamed: J52.A5, R188.2
unnamed: J52.A7, J52.B7, R202.1, U98.1, U98.6
unnamed: J52.A6, J52.B6, R201.1, U98.3, U98.4
unnamed: I2C8.3, R189.2
unnamed: I2C8.1, R190.2
unnamed: C211.2, U89.21, Y9.P3
unnamed: C212.1, R193.1, Y9.P1
unnamed: R193.2, U89.22
unnamed: D25.C, R197.2
unnamed: PWR8.2, R197.1
unnamed: R198.2, U94.5
unnamed: D26.A, R199.1
unnamed: D26.C, U94.1
unnamed: L9.2, U89.48
unnamed: D27.C, R203.2
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
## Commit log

2024-02-13 Add RM2 library file
2024-02-13 Add initial design
2024-02-15 Update Eagle libs
    Add PROD_ID for RM2
    Update Eagle libs for updated version of RT9080 and LM66200
2024-02-16 Remove SD card SDIO
    SDIO can only be achieved via the PIO, and support for it is questionable. Changing to SPI frees up 5 GPIO that can be used for other purposes.
    Change SD card socket to CONN-20948
    Connect SPI pins to SD card socket
    Connect SD card detection pin to GPIO pin
2024-02-16 Fix SD card detection being active high
2024-02-16 Add peripheral power control
    Add a second voltage regulator dedicated to powering the WS2812, uSD card, and Qwiic connector
    Change pinout of A4 and A5 of Thing Plus pinout to make routing easier, and replace RM2 GPIO with RP2350 GPIO
2024-02-16 Connect fuel gauge alert pin
2024-02-16 Design review updates
    Change version number to v02 (significant changes made since v01)
    Add version number to copper
    Add voltage regulator voltage and current specifications to schematic
    Fix swapped POCI and PICO silk
    Add test point for BOOT button
    Fix acid traps
2024-02-20 Design review updates
    Reposition fuel gauge and charge LED to get more clearance around them
    Reposition power LED and resistor for better clearance
    Add fiducials
    Add measures
    Fix TX and RX Buzzard tails
    Fix acid trap
2024-02-20 Improve GND stitching
2024-02-20 Design review updates
    Replace USB ESD diode with larger package for better manufacturing reliability
    Add ordering instructions
2024-02-20 Add proto production files
2024-06-04 Add PSRAM
2024-06-04 Bump version number to v10
2024-06-06 Design review updates
    Rotate EN and BOOT flags to horizontal in schematic
    Add warning about setting SPI pins high while uSD card is unpowered
2024-06-06 Checklist review updates
    Add "Based on design by:"
2024-06-06 Add v10 production files
2024-06-18 Initial docs commit
    Initial docs commit from template
2024-06-27 Hardware overview update
    Hardware overview content for general Thing Plus Hardware.
2024-07-02 Introduction update
    Updating intro from template.
2024-10-29 Docs update
    Initial commit of software sections. Minor updates to hardware overview.
2024-11-13 Docs update
    Adding photo assets & modifying related files.
2024-11-16 Add vision demo
2024-11-18 Tweaks to vision demo
2024-11-18 Use raw mode in vision demo
2024-11-19 Docs photos update
    Adding assembly photo assets & adding them to relevant files. Minor content updates.
2024-11-22 Docs review
    Initial review changes in prep for release.
2024-11-26 Secondary docs review
    Final docs review. Minor edits to hardware overview, intro & micropython sections.
    Adding folder for GH pages actions.
2024-11-27 Update introduction.md
    Adding product showcase video.
2024-11-27 Deployed ffe7f96 with MkDocs version: 1.6.1
2024-12-03 Update micropython_setup.md
    Updating software links for MicroPython Beta firmware.
2024-12-04 Minor documentation update
    Adding updates to Pico SDK & Arduino along w/minor typo fixes.
2024-12-05 Update introduction.md
    Fixing SKU typo.
2024-12-05 Fix battery polarity
    Bump version number to v11
2024-12-05 Panelize v11
2024-12-05 Update README.md
    Fixing README.md overwrite issue.
2024-12-05 LiPo Battery Error Update
    Updating relevant docs files with notes on LiPo battery issue with v10 release.
2024-12-06 Adding Vision Demo
    Adding in vision demo files & photos for documentation.
2024-12-06 Deployed 8dfd966 with MkDocs version: 1.6.1
2025-01-04 Deployed 6e38a0f with MkDocs version: 1.6.1
2025-01-04 Updating battery warnings
    Updating relevant sections with battery warning fix with v11.
2025-01-07 v11 Photos update
    Updating relevant hardware assembly photos with v11 boards.
2025-01-07 yml file fix
    Put the updated action yml in the wrong location. This should fix the build.
2025-01-07 Deployed 8b5d025 with MkDocs version: 1.6.1
2025-01-08 Update file_issue.md
    Fixing link typo
2025-01-08 Deployed b5a47ab with MkDocs version: 1.6.1
